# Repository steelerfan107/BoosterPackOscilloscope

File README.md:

# BoosterPackOscilliscope
An open hardware design sponsored by Texas Instruments to create a Oscilloscope BoosterPack for their LaunchPad series.

#Results

YouTube Videos of Current Version

https://www.youtube.com/watch?v=cYiwDeTmkGY
https://www.youtube.com/watch?v=qeyE9i_el2E
https://www.youtube.com/watch?v=waJ3gXQC8M0
https://www.youtube.com/watch?v=UX_YCJf1Lo4

#Design Files

Contains 
	- Software Files including the Energia Workspace and the Modified Screen Drivers
	- Hardware Files containing EAGLE files of the schematic and board designs. Also included are seperate sheets showing each subsystem.
	- BOM - Bill of Materials

#Reports

Contains
	- All of the reports for this project including
		Project Proposal - Initial project definition 
		Project Plan 	 - Initial schedule of project completeion 
		Decomposition 	 - A breakdown of each subsystem into circuits explaining why parts were used and how
		Final Reort	 - Outlines what worked well and what didnt

#Reserch Memos

Contains
	- Three memos looking into differant aspects of the project.

#Technical Sources

Contains
	- Datasheets of all major parts used

#Testing Plans and Data

Contains
	- Plans to test two subsystems and the results

#User Manual 
	- Contains how to setup project once the board is assembled and fabricated 

If you have any questions just email me at: eric.taylor.9090@gmail.com

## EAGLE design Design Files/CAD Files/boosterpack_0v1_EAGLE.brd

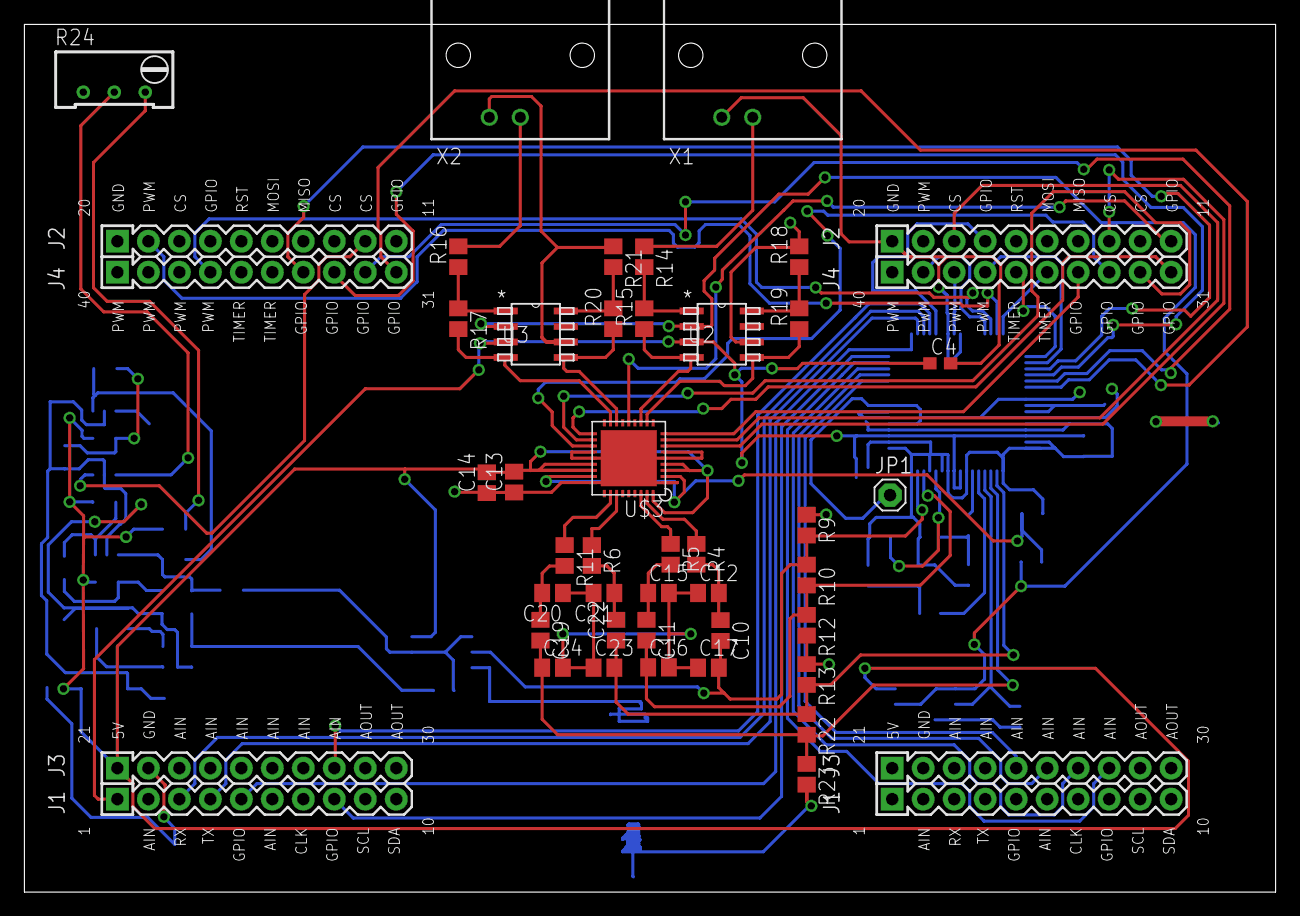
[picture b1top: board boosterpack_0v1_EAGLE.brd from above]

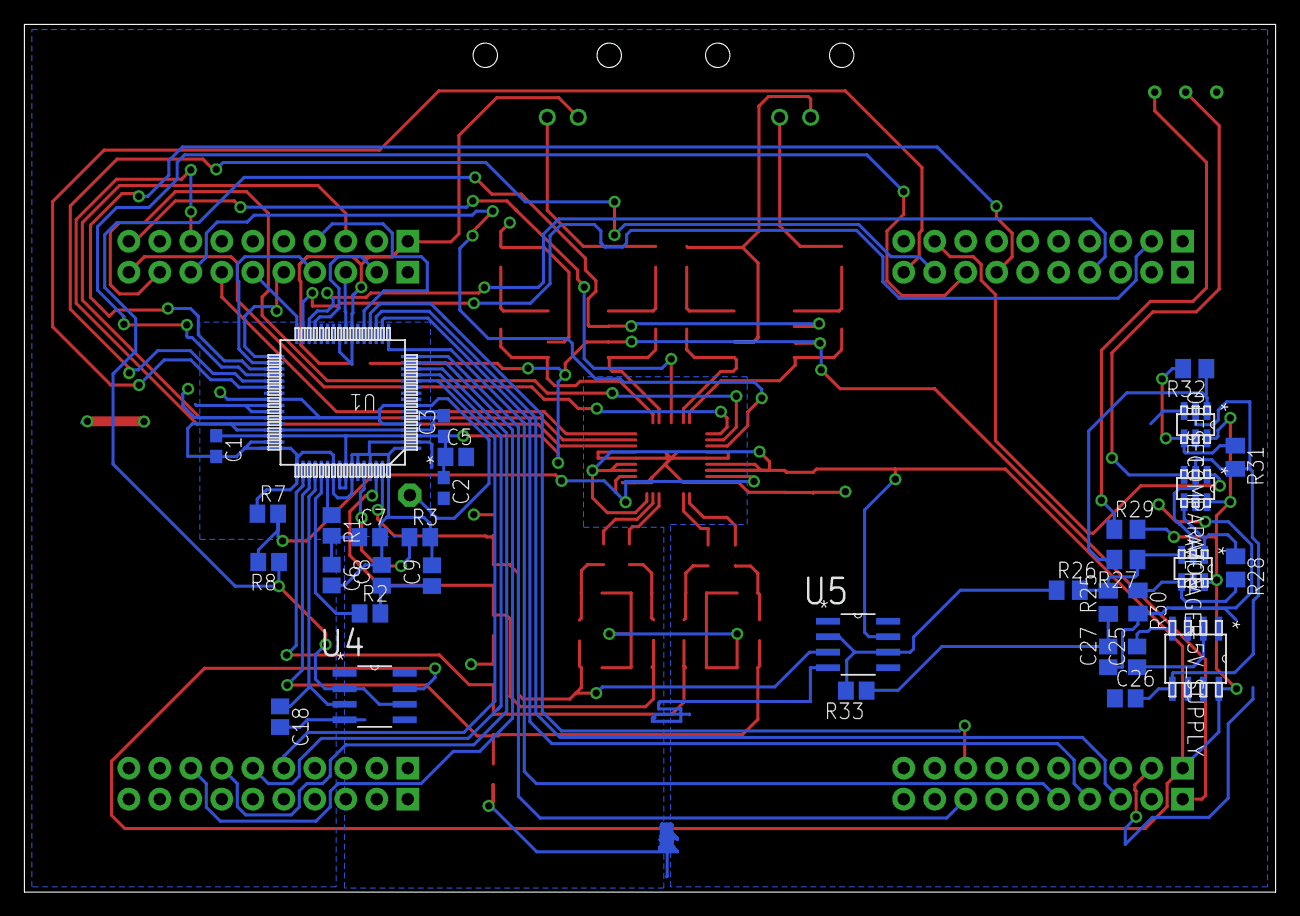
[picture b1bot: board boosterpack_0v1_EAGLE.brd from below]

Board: 2 copper layers, 102.5 x 71.1 mm, 75 parts (33 on the bottom side), 75 nets.

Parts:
-5V_SUPPLY: TL7660_D_8; D8
A1, A2: 4X10-BOOSTERPACK
AVERAGER: OPA890_DBV_6; DBV6
C1, C2, C3, C4: 0.1uF; C0603
C5: 10u; C0805
C6, C8, C18: 0.1u; C0805
C7, C9: 2.2u; C0805
C10, C11, C12, C13, C14, C15, C16, C17, C19, C20, C21, C22, C23, C24, C27: 1000p; C0805
C25, C26: 10uf; C0805
COMPARATOR: OPA890_DBV_6; DBV6
JP1: 1X01
OFFSET: OPA890_DBV_6; DBV6
R1, R2: 2; R0805
R3: 56k; R0805
R4, R5, R6, R11: 50; R0805
R7, R14, R15, R16, R17, R18, R19, R20, R21: 1k; R0805
R8: 200; R0805
R9, R12, R13, R23: 75; R0805
R10, R22: 300; R0805
R24: 10k; RTRIM64W
R25, R26, R27: 1k; M0805
R28: 7.5k; M0805
R29: 2.5k; M0805
R30: 10k; M0805
R31: 5k; M0805
R32: 4k; M0805
R33: 100; R0805
U1: ADS5237_PAG_64; PAG64
U2, U3: THS4121_D_8; D8
U4, U5: OPA140AID; SOIC127P600X175-8N
U$3: LMH6882; WQFN-36-NJK
X1, X2: 1-227161-0; AMP_227161

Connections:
3.3V: A2.1, C1.1, C2.1, C3.1, C4.1, C5.1, U1.3, U1.46, U1.56, U1.57, U2.3, U3.3
A0: A1.25, U1.12
A1: A1.26, U1.13
A2: A1.27, U1.14
A3: A1.28, U1.15
A4: A2.8, U1.16
A5: A2.5, U1.17
A6: A2.4, U1.18
A7: A2.3, U1.19
A8: A2.28, U1.20
A9: A1.17, U1.21
B0: A1.39, U1.29
B1: A2.37, U1.30
B2: A2.19, U1.31
B3: A1.35, U1.32
B4: A1.36, U1.33
B5: A1.37, U1.34
B6: A2.34, U1.35
B7: A2.33, U1.36
B8: A2.32, U1.37
B9: A2.31, U1.38
C0: A1.11, U$3.P$14
C1: A1.13, U$3.P$7
C2: A1.18, U$3.P$8
C3: A1.34, U$3.P$9
C4: A1.33, U$3.P$21
C5: A1.32, U$3.P$20
C6: A1.31, U$3.P$19
GND: -5V_SUPPLY.3, A1.20, A2.20, A2.22, C1.2, C2.2, C3.2, C4.2, C5.2, C6.2, C7.2, C8.2, C9.2, C12.1, C13.1, C14.1, C15.2, C16.2, C17.1, C18.2, C20.1, C21.2, C23.1, C24.2, C26.1, C27.1, OFFSET.3, R3.2, R7.1, R9.1, R12.2, R13.1, R18.2, R21.1, R23.2, R24.1, R30.2, U1.1, U1.2, U1.4, U1.6, U1.7, U1.23, U1.25, U1.41, U1.42, U1.44, U1.45, U1.47, U1.48, U1.49, U1.55, U1.58, U1.59, U1.61, U1.64, U2.6, U3.6, U4.4, U5.4, U$3.P$1, U$3.P$5, U$3.P$6, U$3.P$22, U$3.P$23, U$3.P$27, U$3.TH, X1.2, X2.2
unnamed: A1.38, U1.24
unnamed: JP1.1, U1.5, U1.8, U1.40, U1.43
unnamed: C18.1, U1.52, U4.3
unnamed: C19.2, C24.1, R22.2, R23.1, U1.51
unnamed: R24.3, R29.1
unnamed: COMPARATOR.3, R24.2
unnamed: AVERAGER.4, R28.2, R30.1
unnamed: C11.1, C15.1, R5.2
unnamed: R8.1, U2.2, U3.2, U4.2, U4.6
unnamed: R7.2, R8.2, U$3.P$2, U$3.P$26
unnamed: AVERAGER.3, R25.2, R26.2, R27.1
unnamed: C11.2, C16.1, R10.2, R12.1, U1.62
unnamed: C21.1, C22.2, R6.2
unnamed: C19.1, C20.2, R11.2
unnamed: AVERAGER.1, COMPARATOR.4, R28.1
unnamed: C22.1, C23.2, R13.2, R22.1, U1.50
unnamed: OFFSET.1, R27.2, R32.1
unnamed: OFFSET.4, R31.1, R32.2
unnamed: R5.1, U$3.P$34
unnamed: R26.1, R33.2, U5.2, U5.6
unnamed: -5V_SUPPLY.2, C25.1
unnamed: -5V_SUPPLY.4, C25.2
unnamed: -5V_SUPPLY.5, AVERAGER.2, C26.2, COMPARATOR.2, OFFSET.2, R31.2
unnamed: C10.2, C17.2, R9.2, R10.1, U1.63, U5.3
unnamed: R4.1, U$3.P$35
unnamed: C6.1, C7.1, R1.2
unnamed: C8.1, C9.1, R2.2
unnamed: R1.1, U1.54
unnamed: R2.1, U1.53
unnamed: R3.1, U1.60
unnamed: R14.1, X1.1
unnamed: R6.1, U$3.P$30
unnamed: R14.2, R15.2, U2.1
unnamed: R15.1, U2.4, U$3.P$12
unnamed: R16.1, R17.1, U3.1
unnamed: R17.2, U3.4, U$3.P$17
unnamed: R18.1, R19.2, U2.8
unnamed: R20.2, R21.2, U3.8
unnamed: R16.2, X2.1
unnamed: R20.1, U3.5, U$3.P$16
unnamed: R19.1, U2.5, U$3.P$11
unnamed: R11.1, U$3.P$29
unnamed: C10.1, C12.2, R4.2
OUTPUT: A2.12, COMPARATOR.1
SIGNAL1: C27.2, R25.1, R33.1
VCC: -5V_SUPPLY.8, A2.21, AVERAGER.6, C13.2, C14.2, COMPARATOR.6, OFFSET.6, R29.2, U4.7, U5.7, U$3.P$3, U$3.P$4, U$3.P$24, U$3.P$25, U$3.P$36

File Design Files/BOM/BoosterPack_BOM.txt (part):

Partlist exported from C:/Users/Eric/Desktop/Team04ScopeBoosterpack/ProjectFiles/Design Files/Schematics/boosterpack_0v1_EAGLE_sch.sch at 4/23/2015 1:21:57 PM

Part       Value          Device                 Package            Description                          C     DATASHEETURL                      DESCRIPTION                                                              FAMILY_NAME                  GENERIC_PART_NUMBER INDUSTRY_STD_PKG_TYPE MANUFACTURER      MANUFACTURER_PART_NUMBER MF               MPN       OC_FARNELL OC_NEWARK PACKAGE PACKAGE_DESIGNATOR PIN_COUNT SUPPLIER          VENDOR           
-5V_SUPPLY TL7660_D_8     TL7660_D_8             D8                                                            http://www.ti.com/lit/gpn/TL7660  CMOS Voltage Converter                                                   LOW POWER                    TL7660              SOIC                  Texas Instruments tl7660_d_8                                                                       D                  8                           Texas Instruments
A1                        HEADER4X10-BOOSTERPACK 4X10-BOOSTERPACK                                                                                                                                                                                                                                                                                                                                                                                                   
A2                        HEADER4X10-BOOSTERPACK 4X10-BOOSTERPACK                                                                                                                                                                                                                                                                                                                                                                                                   
AVERAGER   OPA890_DBV_6   OPA890_DBV_6           DBV6                                                          http://www.ti.com/lit/gpn/OPA890  Low Power, Wideband, Voltage Feedback Operational Amplifier with Disable VOLTAGE FEEDBACK             OPA890              SOT-23                Texas Instruments opa890_dbv_6                                                                     DBV                6                           Texas Instruments
C1         0.1uF          C-USC0603              C0603              CAPACITOR, American symbol                                                                                                                                                                                                                                                                                                                                                                      
C2         0.1uF          C-USC0603              C0603              CAPACITOR, American symbol                                                                                                                                                                                                                                                                                                                                                                      
C3         0.1uF          C-USC0603              C0603              CAPACITOR, American symbol                                                                                                                                                                                                                                                                                                                                                                      
C4         0.1uF          C-USC0603              C0603              CAPACITOR, American symbol                                                                                                                                                                                                                                                                                                                                                                      
C5         10u            C-USC0805              C0805              CAPACITOR, American symbol           10uF                                                                                                                                                                                                                                                                                                                                                       
C6         0.1u           C-USC0805              C0805              CAPACITOR, American symbol                                                                                                                                                                                                                                                                                                                                                                      
C7         2.2u           C-USC0805              C0805              CAPACITOR, American symbol                                                                                                                                                                                                                                                                                                                                                                      
C8         0.1u           C-USC0805              C0805              CAPACITOR, American symbol                                                                                                                                                                                                                                                                                                                                                                      
C9         2.2u           C-USC0805              C0805              CAPACITOR, American symbol                                                                                                                                                                                                                                                                                                                                                                      
C10        1000p          C-USC0805              C0805              CAPACITOR, American symbol                                                                                                                                                                                                                                                                                                                                                                      
C11        1000p          C-USC0805              C0805              CAPACITOR, American symbol                                                                                                                                                                                                                                                                                                                                                                      
C12        1000p          C-USC0805              C0805              CAPACITOR, American symbol                                                                                                                                                                                                                                                                                                                                                                      
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
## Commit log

2015-04-23 Upload
2015-04-23 Small
2015-05-26 ti rpeort
